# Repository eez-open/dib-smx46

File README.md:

The EEZ DIB SMX46 module features programmable 4 x 6 switch matrix,  dual analog outputs and one power relay. 

### Feature list

* On-board STM32F030C6T6 or STM32F031C4T6 MCU
* 2 x 16-pin dual row 3.81 mm connectors
* 2 x ADIB connectors (10-pin 2 mm)
* 4 x 6 switch matrix (24 two-wire crosspoints), max. 2 A 
* 1 x power relay, max. 8 A / 230 Vac
* 2 x analog output 0 - 10 V, 10 mV set resolution (12-bit)
* On-board +3.3 V LDO
* Firmware download via UART
* Optional SWD for debugging
* I2C EEPROM for storing board specific parameters
* Dimensions: 146 x 95 mm, 2-layer PCB

### Firmware repository

https://github.com/eez-open/dib-smx46-fw

### r1B5 prototype

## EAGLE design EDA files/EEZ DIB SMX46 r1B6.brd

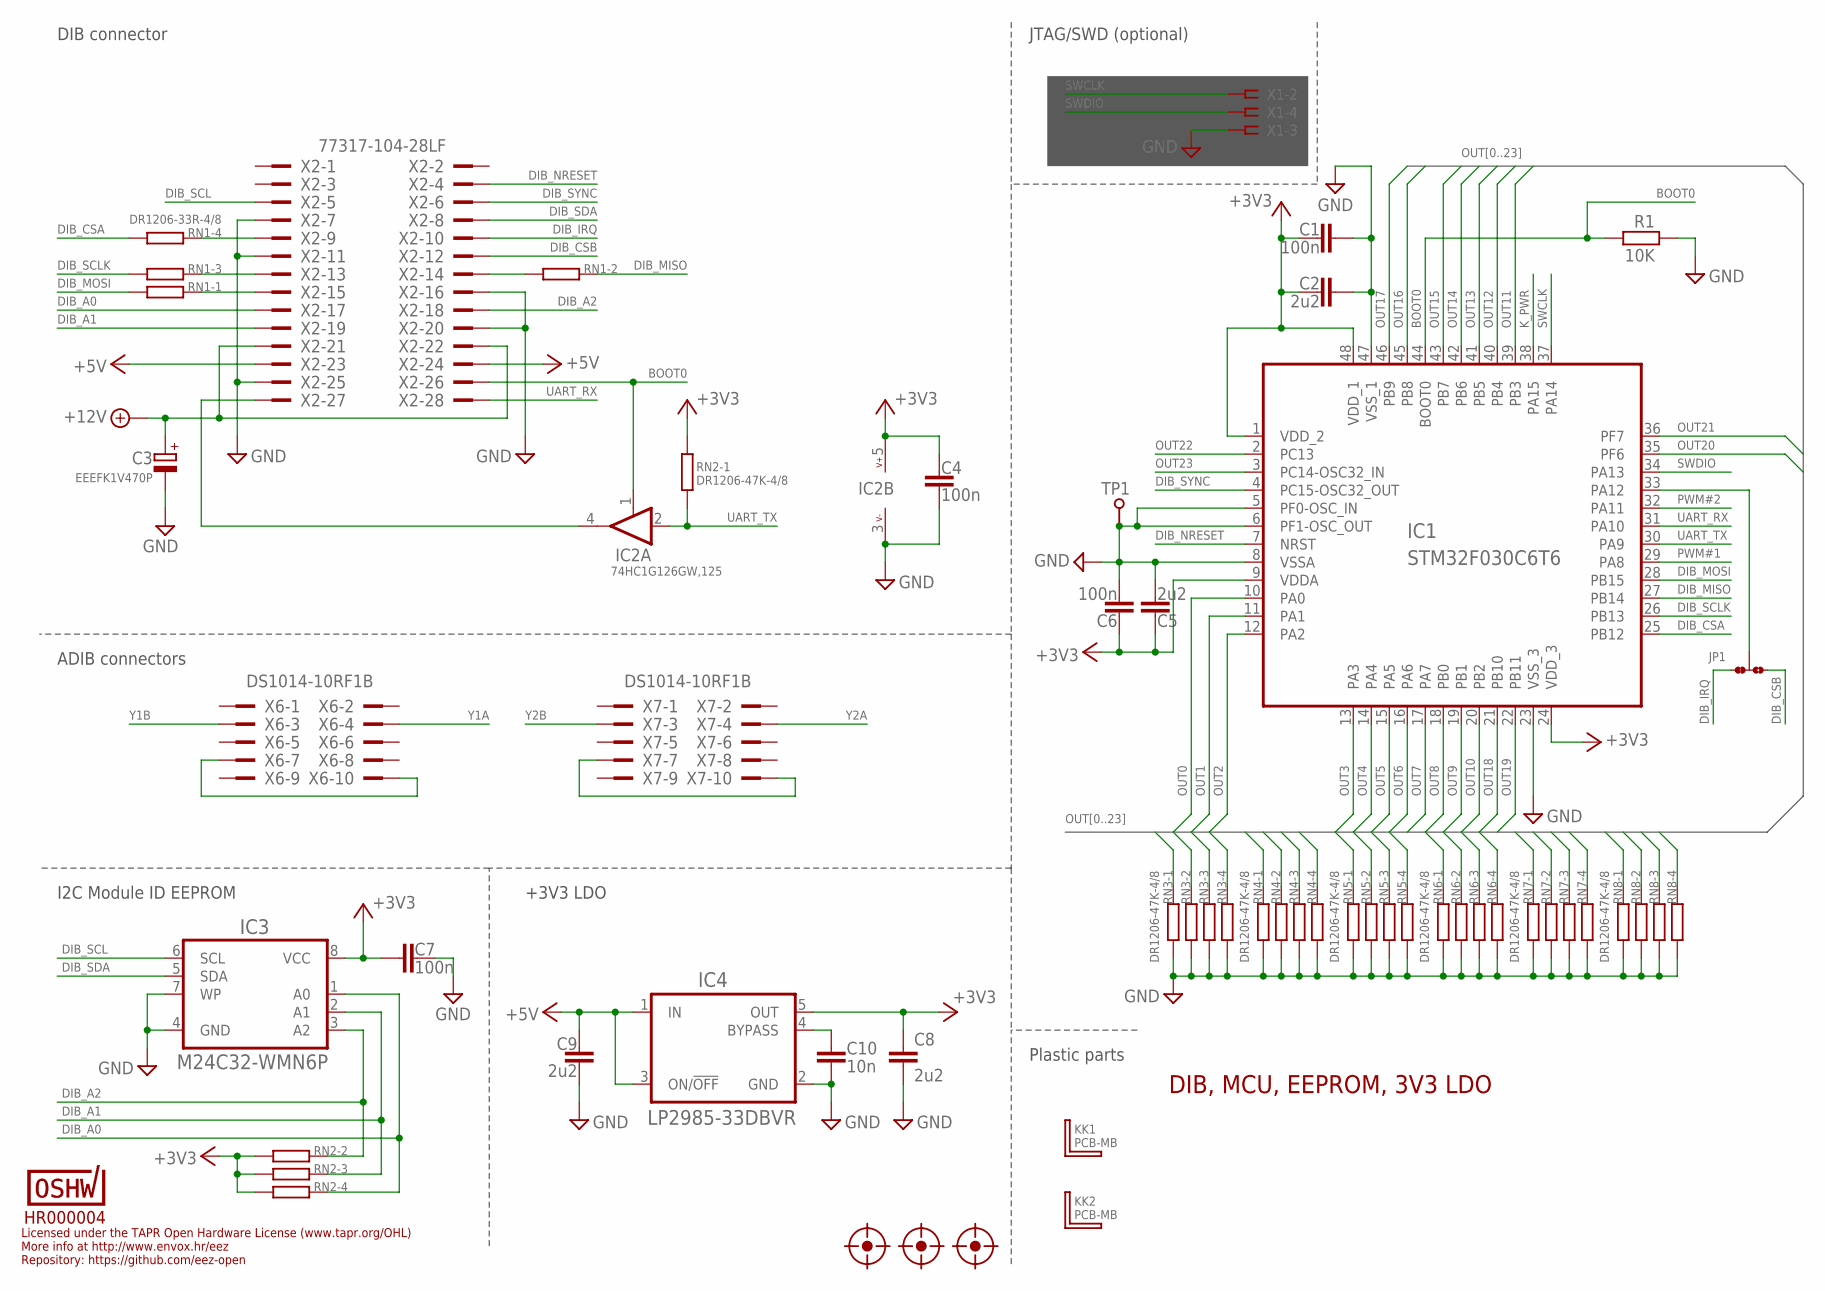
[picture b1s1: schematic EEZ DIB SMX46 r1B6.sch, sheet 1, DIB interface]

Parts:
C1, C4, C6, C7: 100n; C0603
C2, C5, C8, C9: 2u2; C0805
C3: EEEFK1V470P; CAPAE660X610N
C10: 10n; C0805
FM1, FM2, FM3: FIDUCIAL_2; FIDUCIAL_DUAL
IC1: STM32F030C6T6; LQFP-48
IC2: 74HC1G126GW,125; SOT65P210X110-5N
IC3: M24C32-WMN6P; SOIC127P600X173-8N
IC4: LP2985-33DBVR; SOT95P270X145-5N
JP1: JP3-CUT-0805-ROTATED; JP3-0805-CUT2
KK1, KK2: PCB-MB
R1: 10K; R0805
RN1: DR1206-33R-4/8; CAY16
RN2, RN3, RN4, RN5, RN6, RN7, RN8: DR1206-47K-4/8; CAY16
TP1: PCB_TEST_TABSHIELD; PCB_SHIELD_TAB
U$3: HR000004; CERT-SMALL-SILK
X1: N.C.; SSW-106-02-S-S
X2: 77317-104-28LF
X6, X7: DS1014-10RF1B

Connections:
+3V3: C1.2, C2.1, C4.1, C5.2, C6.1, C7.2, C8.1, IC1.1 (VDD_2), IC1.9 (VDDA), IC1.24 (VDD_3), IC1.48 (VDD_1), IC2.5 (V+), IC3.8 (VCC), IC4.5 (OUT), RN2.5 (2), RN2.6 (2), RN2.7 (2), RN2.8 (2); also elsewhere on the board
+5V: C9.2, IC4.1 (IN), IC4.3 (ON/!OFF), X2.23, X2.24; also elsewhere on the board
+12V: C3.1 (+), X2.21, X2.22; also elsewhere on the board
BOOT0: IC1.44 (BOOT0), IC2.1 (EN), R1.2, X2.26
DIB_A0: IC3.1 (A0), RN2.4 (1), X2.17
DIB_A1: IC3.2 (A1), RN2.3 (1), X2.19
DIB_A2: IC3.3 (A2), RN2.2 (1), X2.18
DIB_CSA: IC1.25 (PB12), RN1.4 (1)
DIB_CSB: JP1.NO, X2.12
DIB_IRQ: JP1.NC, X2.10
DIB_MISO: IC1.27 (PB14), RN1.2 (1)
DIB_MOSI: IC1.28 (PB15), RN1.1
DIB_NRESET: IC1.7 (NRST), X2.4
DIB_SCL: IC3.6 (SCL), X2.5
DIB_SCLK: IC1.26 (PB13), RN1.3 (1)
DIB_SDA: IC3.5 (SDA), X2.8
DIB_SYNC: IC1.4 (PC15-OSC32_OUT), X2.6
GND: C1.1, C2.2, C3.2 (-), C4.2, C5.1, C6.2, C7.1, C8.2, C9.1, C10.1, IC1.5 (PF0-OSC_IN), IC1.6 (PF1-OSC_OUT), IC1.8 (VSSA), IC1.23 (VSS_3), IC1.47 (VSS_1), IC2.3 (V-), IC3.4 (GND), IC3.7 (WP), IC4.2 (GND), R1.1, RN3.1, RN3.2 (1), RN3.3 (1), RN3.4 (1), RN4.1, RN4.2 (1), RN4.3 (1), RN4.4 (1), RN5.1, RN5.2 (1), RN5.3 (1), RN5.4 (1), RN6.1, RN6.2 (1), RN6.3 (1), RN6.4 (1), RN7.3 (1), RN7.4 (1), RN7.7 (2), RN7.8 (2), RN8.3 (1), RN8.4 (1), RN8.7 (2), RN8.8 (2), TP1.1, X1.3, X2.7, X2.11, X2.16, X2.20, X2.25; also elsewhere on the board
K_PWR: IC1.38 (PA15); also elsewhere on the board
unnamed: X6.7, X6.10
unnamed: X7.7, X7.10
unnamed: RN1.5 (2), X2.9
unnamed: C10.2, IC4.4 (BYPASS)
unnamed: IC2.4 (O), X2.27
unnamed: IC1.33 (PA12), JP1.COM
unnamed: RN1.6 (2), X2.13
unnamed: RN1.7 (2), X2.14
unnamed: RN1.8 (2), X2.15
OUT0: IC1.10 (PA0), RN3.8 (2); also elsewhere on the board
OUT1: IC1.11 (PA1), RN3.7 (2); also elsewhere on the board
OUT2: IC1.12 (PA2), RN6.8 (2); also elsewhere on the board
OUT3: IC1.13 (PA3), RN6.7 (2); also elsewhere on the board
OUT4: IC1.14 (PA4), RN3.5 (2); also elsewhere on the board
OUT5: IC1.15 (PA5), RN3.6 (2); also elsewhere on the board
OUT6: IC1.16 (PA6), RN6.5 (2); also elsewhere on the board
OUT7: IC1.17 (PA7), RN6.6 (2); also elsewhere on the board
OUT8: IC1.18 (PB0), RN4.7 (2); also elsewhere on the board
OUT9: IC1.19 (PB1), RN4.8 (2); also elsewhere on the board
OUT10: IC1.20 (PB2), RN7.6 (2); also elsewhere on the board
OUT11: IC1.39 (PB3), RN7.5 (2); also elsewhere on the board
OUT12: IC1.40 (PB4), RN4.5 (2); also elsewhere on the board
OUT13: IC1.41 (PB5), RN4.6 (2); also elsewhere on the board
OUT14: IC1.42 (PB6), RN7.2 (1); also elsewhere on the board
OUT15: IC1.43 (PB7), RN7.1; also elsewhere on the board
OUT16: IC1.45 (PB8), RN5.7 (2); also elsewhere on the board
OUT17: IC1.46 (PB9), RN5.8 (2); also elsewhere on the board
OUT18: IC1.21 (PB10), RN8.5 (2); also elsewhere on the board
OUT19: IC1.22 (PB11), RN8.6 (2); also elsewhere on the board
OUT20: IC1.35 (PF6), RN5.5 (2); also elsewhere on the board
OUT21: IC1.36 (PF7), RN5.6 (2); also elsewhere on the board
OUT22: IC1.2 (PC13), RN8.1; also elsewhere on the board
OUT23: IC1.3 (PC14-OSC32_IN), RN8.2 (1); also elsewhere on the board
PWM#1: IC1.29 (PA8); also elsewhere on the board
PWM#2: IC1.32 (PA11); also elsewhere on the board
SWCLK: IC1.37 (PA14), X1.2
SWDIO: IC1.34 (PA13), X1.4
UART_RX: IC1.31 (PA10), X2.28
UART_TX: IC1.30 (PA9), IC2.2 (I), RN2.1
Y1A: X6.4; also elsewhere on the board
Y1B: X6.3; also elsewhere on the board
Y2A: X7.4; also elsewhere on the board
Y2B: X7.3; also elsewhere on the board

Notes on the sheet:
Licensed under the TAPR Open Hardware License (www.tapr.org/OHL)
Repository: https://github.com/eez-open
More info at http://www.envox.hr/eez
DIB, MCU, EEPROM, 3V3 LDO
Plastic parts
I2C Module ID EEPROM
+3V3 LDO
JTAG/SWD (optional)
DIB connector
ADIB connectors

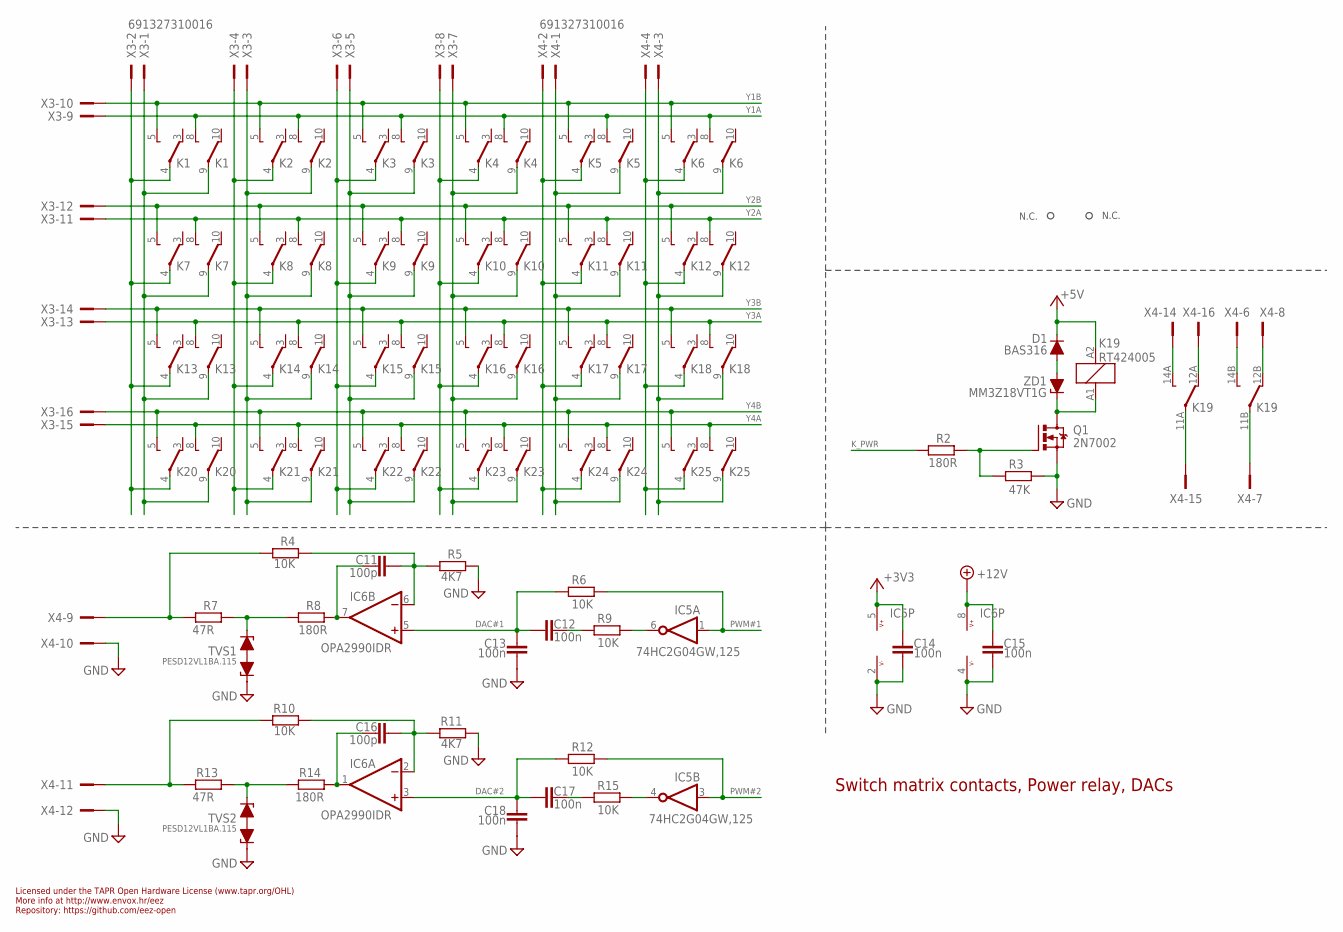
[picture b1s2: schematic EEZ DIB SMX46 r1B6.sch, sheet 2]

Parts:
C11, C16: 100p; C0805
C12, C13, C14, C15, C17, C18: 100n; C0603
D1: BAS316; SOD323-R
IC5: 74HC2G04GW,125; SOT65P210X110-6N
IC6: OPA2990IDR; SOIC127P600X173-8N
K1, K2, K3, K4, K5, K6, K7, K8, K9, K10, K11, K12, K13, K14, K15, K16, K17, K18, K20, K21, K22, K23, K24, K25: FTR-C1GA012G-B05; FTR-C1
K19: RT424005; RT-C/016A5_ROUND
Q1: 2N7002; SOT103P240X110-3N; MPN 2N7002-7-F
R2, R8, R14: 180R; R0805
R3: 47K; R0805
R4, R6, R9, R10, R12, R15: 10K; R0805
R5, R11: 4K7; R0805
R7, R13: 47R; R0805
TVS1, TVS2: PESD12VL1BA.115; SOD323-BIDIR
X3, X4: 691327310016
ZD1: MM3Z18VT1G; SOD323-R

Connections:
+3V3: C14.1, IC5.5 (V+); also elsewhere on the board
+5V: D1.C, K19.A2 (C1); also elsewhere on the board
+12V: C15.1, IC6.8 (V+); also elsewhere on the board
DAC#1: C12.1, C13.1, IC6.5 (+IN), R6.1
DAC#2: C17.1, C18.1, IC6.3 (+IN), R12.1
GND: C13.2, C14.2, C15.2, C18.2, IC5.2 (V-), IC6.4 (V-), Q1.2 (S), R3.1, R5.1, R11.1, TVS1.1, TVS2.1, X4.10, X4.12; also elsewhere on the board
ISET1: R7.1, R8.2, TVS1.2
ISET2: R13.1, R14.2, TVS2.2
K_PWR: R2.2; also elsewhere on the board
unnamed: K1.4, K7.4, K13.4, K20.4, X3.2
unnamed: K1.9, K7.9, K13.9, K20.9, X3.1
unnamed: K5.4, K11.4, K17.4, K24.4, X4.2
unnamed: K2.4, K8.4, K14.4, K21.4, X3.4
unnamed: K2.9, K8.9, K14.9, K21.9, X3.3
unnamed: K5.9, K11.9, K17.9, K24.9, X4.1
unnamed: K6.4, K12.4, K18.4, K25.4, X4.4
unnamed: K6.9, K12.9, K18.9, K25.9, X4.3
unnamed: K3.4, K9.4, K15.4, K22.4, X3.6
unnamed: K3.9, K9.9, K15.9, K22.9, X3.5
unnamed: K4.4, K10.4, K16.4, K23.4, X3.8
unnamed: K4.9, K10.9, K16.9, K23.9, X3.7
unnamed: R4.2, R7.2, X4.9
unnamed: C17.2, R15.1
unnamed: IC5.4 (O), R15.2
unnamed: C11.1, IC6.7 (OUT), R8.1
unnamed: C16.2, IC6.2 (-IN), R10.1, R11.2
unnamed: Q1.1 (G), R2.1, R3.2
unnamed: C16.1, IC6.1 (OUT), R14.1
unnamed: K19.11B, X4.7
unnamed: K19.12B (S), X4.8
unnamed: R10.2, R13.2, X4.11
unnamed: K19.14B (O), X4.6
unnamed: K19.11A, X4.15
unnamed: K19.12A (S), X4.16
unnamed: K19.14A (O), X4.14
unnamed: D1.A, ZD1.A
unnamed: K19.A1 (C2), Q1.3 (D), ZD1.C
unnamed: C12.2, R9.1
unnamed: C11.2, IC6.6 (-IN), R4.1, R5.2
unnamed: IC5.6 (O), R9.2
PWM#1: IC5.1 (I), R6.2; also elsewhere on the board
PWM#2: IC5.3 (I), R12.2; also elsewhere on the board
Y1A: K1.8 (O), K2.8 (O), K3.8 (O), K4.8 (O), K5.8 (O), K6.8 (O), X3.9; also elsewhere on the board
Y1B: K1.5 (O), K2.5 (O), K3.5 (O), K4.5 (O), K5.5 (O), K6.5 (O), X3.10; also elsewhere on the board
Y2A: K7.8 (O), K8.8 (O), K9.8 (O), K10.8 (O), K11.8 (O), K12.8 (O), X3.11; also elsewhere on the board
Y2B: K7.5 (O), K8.5 (O), K9.5 (O), K10.5 (O), K11.5 (O), K12.5 (O), X3.12; also elsewhere on the board
Y3A: K13.8 (O), K14.8 (O), K15.8 (O), K16.8 (O), K17.8 (O), K18.8 (O), X3.13
Y3B: K13.5 (O), K14.5 (O), K15.5 (O), K16.5 (O), K17.5 (O), K18.5 (O), X3.14
Y4A: K20.8 (O), K21.8 (O), K22.8 (O), K23.8 (O), K24.8 (O), K25.8 (O), X3.15
Y4B: K20.5 (O), K21.5 (O), K22.5 (O), K23.5 (O), K24.5 (O), K25.5 (O), X3.16

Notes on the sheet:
Licensed under the TAPR Open Hardware License (www.tapr.org/OHL)
Repository: https://github.com/eez-open
More info at http://www.envox.hr/eez
Switch matrix contacts, Power relay, DACs
N.C.

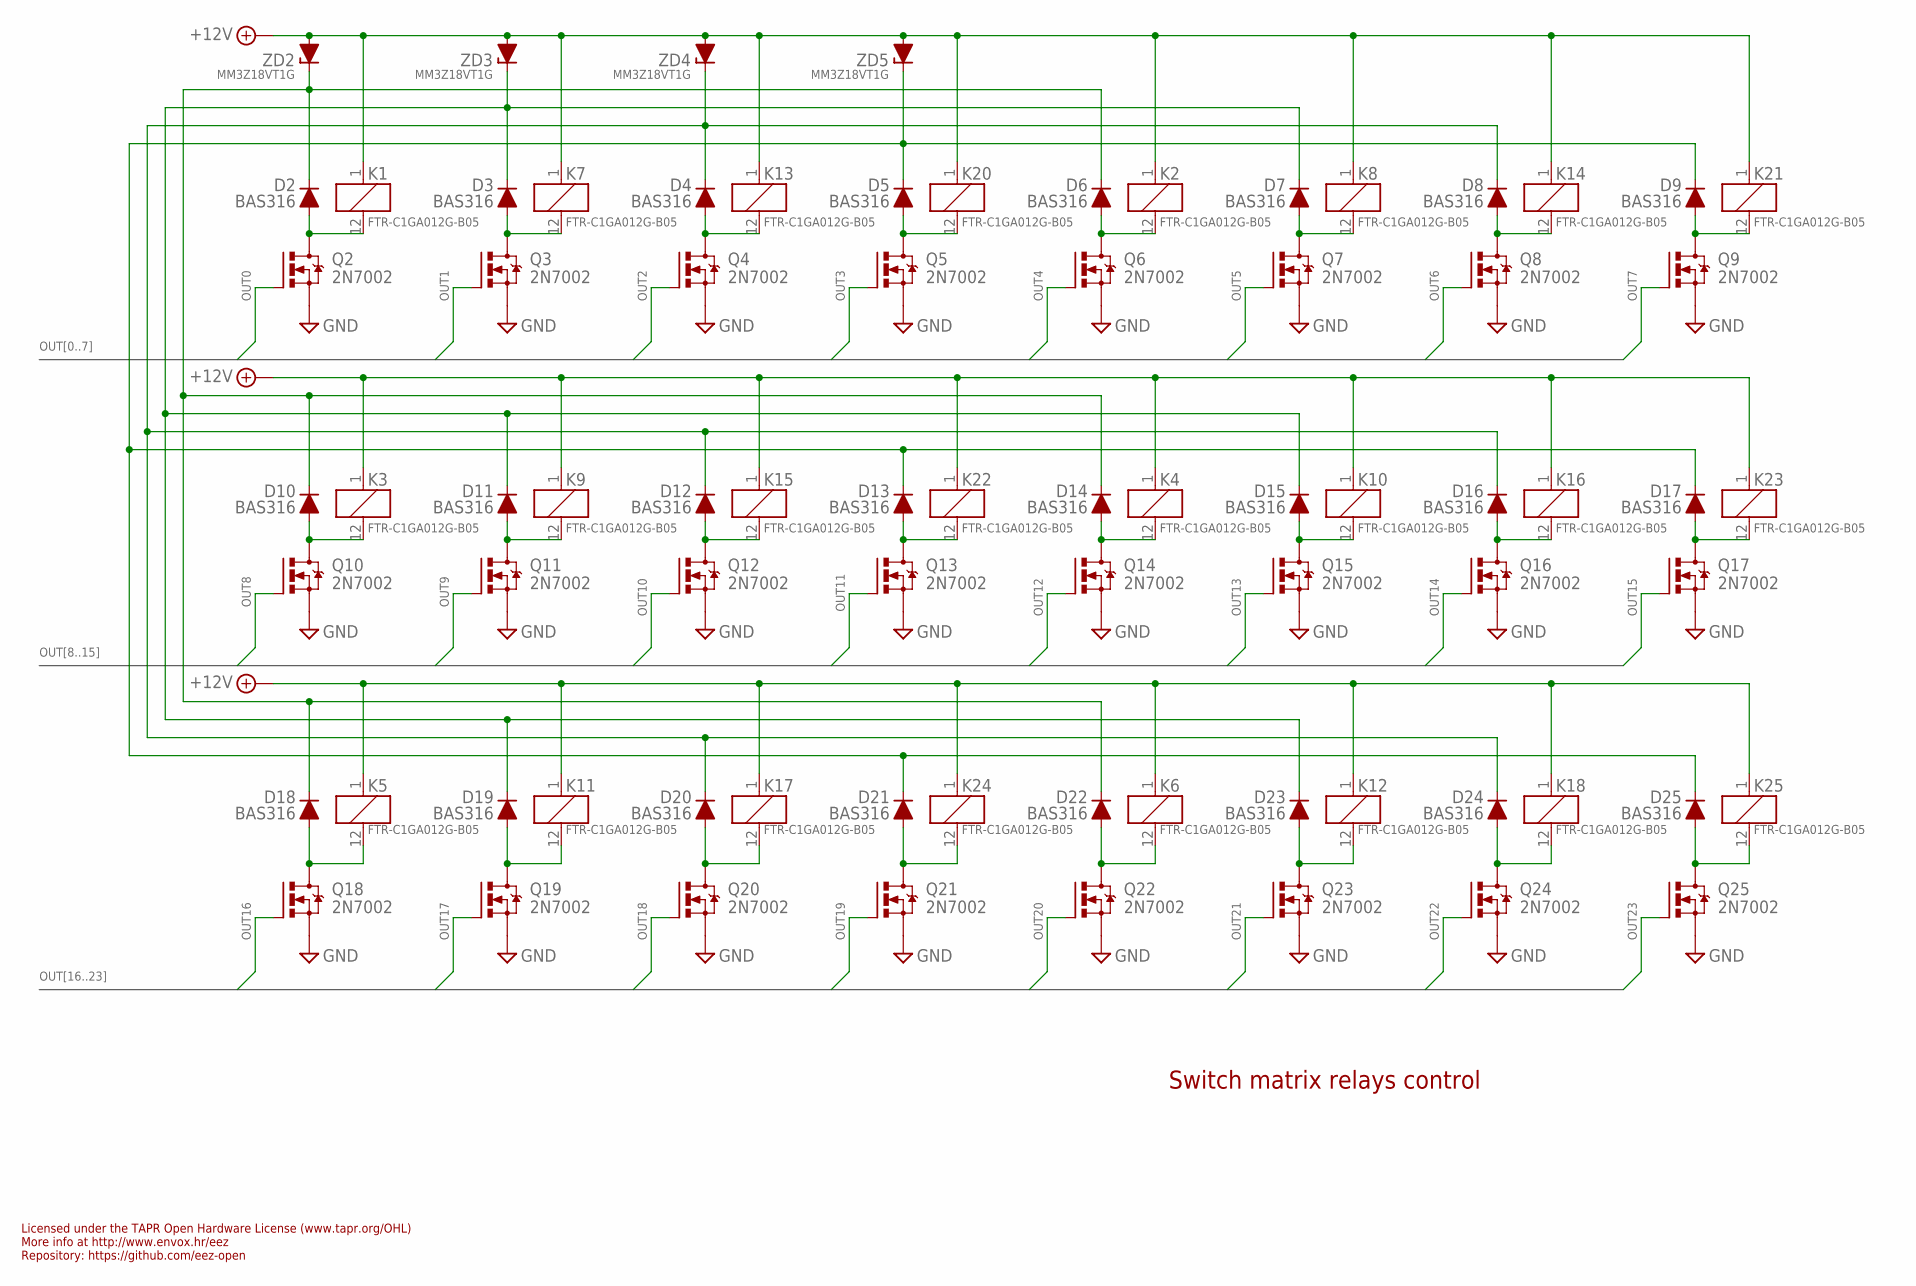
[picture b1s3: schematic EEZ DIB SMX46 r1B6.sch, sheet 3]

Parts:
D2, D3, D4, D5, D6, D7, D8, D9, D10, D11, D12, D13, D14, D15, D16, D17, D18, D19, D20, D21, D22, D23, D24, D25: BAS316; SOD323-R
K1, K2, K3, K4, K5, K6, K7, K8, K9, K10, K11, K12, K13, K14, K15, K16, K17, K18, K20, K21, K22, K23, K24, K25: FTR-C1GA012G-B05; FTR-C1
Q2, Q3, Q4, Q5, Q6, Q7, Q8, Q9, Q10, Q11, Q12, Q13, Q14, Q15, Q16, Q17, Q18, Q19, Q20, Q21, Q22, Q23, Q24, Q25: 2N7002; SOT103P240X110-3N; MPN 2N7002-7-F
ZD2, ZD3, ZD4, ZD5: MM3Z18VT1G; SOD323-R

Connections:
+12V: K1.1 (C1), K2.1 (C1), K3.1 (C1), K4.1 (C1), K5.1 (C1), K6.1 (C1), K7.1 (C1), K8.1 (C1), K9.1 (C1), K10.1 (C1), K11.1 (C1), K12.1 (C1), K13.1 (C1), K14.1 (C1), K15.1 (C1), K16.1 (C1), K17.1 (C1), K18.1 (C1), K20.1 (C1), K21.1 (C1), K22.1 (C1), K23.1 (C1), K24.1 (C1), K25.1 (C1), ZD2.A, ZD3.A, ZD4.A, ZD5.A; also elsewhere on the board
GND: Q2.2 (S), Q3.2 (S), Q4.2 (S), Q5.2 (S), Q6.2 (S), Q7.2 (S), Q8.2 (S), Q9.2 (S), Q10.2 (S), Q11.2 (S), Q12.2 (S), Q13.2 (S), Q14.2 (S), Q15.2 (S), Q16.2 (S), Q17.2 (S), Q18.2 (S), Q19.2 (S), Q20.2 (S), Q21.2 (S), Q22.2 (S), Q23.2 (S), Q24.2 (S), Q25.2 (S); also elsewhere on the board
unnamed: D2.C, D6.C, D10.C, D14.C, D18.C, D22.C, ZD2.C
unnamed: D3.C, D7.C, D11.C, D15.C, D19.C, D23.C, ZD3.C
unnamed: D4.C, D8.C, D12.C, D16.C, D20.C, D24.C, ZD4.C
unnamed: D5.C, D9.C, D13.C, D17.C, D21.C, D25.C, ZD5.C
unnamed: D4.A, K13.12 (C2), Q4.3 (D)
unnamed: D8.A, K14.12 (C2), Q8.3 (D)
unnamed: D10.A, K3.12 (C2), Q10.3 (D)
unnamed: D9.A, K21.12 (C2), Q9.3 (D)
unnamed: D11.A, K9.12 (C2), Q11.3 (D)
unnamed: D7.A, K8.12 (C2), Q7.3 (D)
unnamed: D12.A, K15.12 (C2), Q12.3 (D)
unnamed: D6.A, K2.12 (C2), Q6.3 (D)
unnamed: D13.A, K22.12 (C2), Q13.3 (D)
unnamed: D3.A, K7.12 (C2), Q3.3 (D)
unnamed: D14.A, K4.12 (C2), Q14.3 (D)
unnamed: D2.A, K1.12 (C2), Q2.3 (D)
unnamed: D15.A, K10.12 (C2), Q15.3 (D)
unnamed: D5.A, K20.12 (C2), Q5.3 (D)
unnamed: D16.A, K16.12 (C2), Q16.3 (D)
unnamed: D17.A, K23.12 (C2), Q17.3 (D)
unnamed: D19.A, K11.12 (C2), Q19.3 (D)
unnamed: D20.A, K17.12 (C2), Q20.3 (D)
unnamed: D21.A, K24.12 (C2), Q21.3 (D)
unnamed: D22.A, K6.12 (C2), Q22.3 (D)
unnamed: D23.A, K12.12 (C2), Q23.3 (D)
unnamed: D18.A, K5.12 (C2), Q18.3 (D)
unnamed: D24.A, K18.12 (C2), Q24.3 (D)
unnamed: D25.A, K25.12 (C2), Q25.3 (D)
OUT0: Q2.1 (G); also elsewhere on the board
OUT1: Q3.1 (G); also elsewhere on the board
OUT2: Q4.1 (G); also elsewhere on the board
OUT3: Q5.1 (G); also elsewhere on the board
OUT4: Q6.1 (G); also elsewhere on the board
OUT5: Q7.1 (G); also elsewhere on the board
OUT6: Q8.1 (G); also elsewhere on the board
OUT7: Q9.1 (G); also elsewhere on the board
OUT8: Q10.1 (G); also elsewhere on the board
OUT9: Q11.1 (G); also elsewhere on the board
OUT10: Q12.1 (G); also elsewhere on the board
OUT11: Q13.1 (G); also elsewhere on the board
OUT12: Q14.1 (G); also elsewhere on the board
OUT13: Q15.1 (G); also elsewhere on the board
OUT14: Q16.1 (G); also elsewhere on the board
OUT15: Q17.1 (G); also elsewhere on the board
OUT16: Q18.1 (G); also elsewhere on the board
OUT17: Q19.1 (G); also elsewhere on the board
OUT18: Q20.1 (G); also elsewhere on the board
OUT19: Q21.1 (G); also elsewhere on the board
OUT20: Q22.1 (G); also elsewhere on the board
OUT21: Q23.1 (G); also elsewhere on the board
OUT22: Q24.1 (G); also elsewhere on the board
OUT23: Q25.1 (G); also elsewhere on the board

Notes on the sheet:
Licensed under the TAPR Open Hardware License (www.tapr.org/OHL)
Repository: https://github.com/eez-open
More info at http://www.envox.hr/eez
Switch matrix relays control

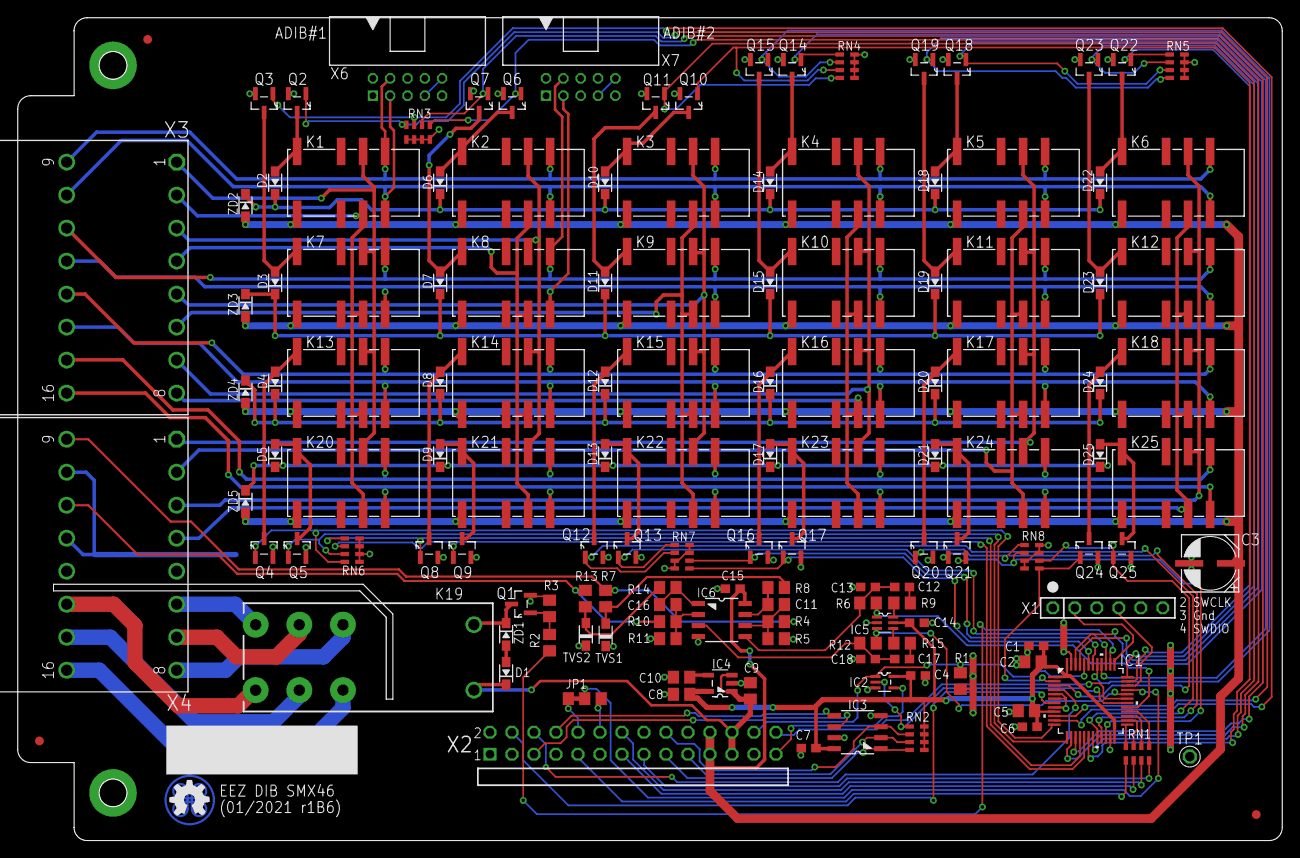
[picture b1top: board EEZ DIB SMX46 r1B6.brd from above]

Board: 2 copper layers, 146.0 x 95.0 mm, 144 parts (1 on the bottom side), 129 nets.

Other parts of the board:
EEZ_SIGNATURE: SIGNATURESMALL; SIGNATURE_5MM

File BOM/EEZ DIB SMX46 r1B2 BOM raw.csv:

Partlist exported from /home/denis/BACKUP/EEZ/PCB/Programmable PSU/DIB/EEZ DIB SMX46 r1B2.sch at 6.4.2020. 12:41

Assembly variant: ''

Qty Value            Device             Parts                                                                                                                                      
1   1u               C-EUC0805          C6                                                                                                                                         
25  2N7002           2N7002             Q1, Q2, Q3, Q4, Q5, Q6, Q7, Q8, Q9, Q10, Q11, Q12, Q13, Q14, Q15, Q16, Q17, Q18, Q19, Q20, Q21, Q22, Q23, Q24, Q25                         
1   2u2              C-EUC0805          C8                                                                                                                                         
2   4K7              R-EU_R0805         R4, R10                                                                                                                                    
2   4u7              C-EUC0805          C2, C9                                                                                                                                     
7   10K              R-EU_R0805         R1, R3, R5, R8, R9, R11, R14                                                                                                               
1   10n              C-EUC0805          C10                                                                                                                                        
1   47K              R-EU_R0805         R2                                                                                                                                         
2   47R              R-EU_R0805         R6, R12                                                                                                                                    
1   74HC1G126GW,125  74HC1G126GW,125    IC2                                                                                                                                        
1   74HC2G04GW,125   74HC2G04           IC5                                                                                                                                        
10  100n             C-EUC0603          C1, C4, C5, C7, C12, C13, C14, C15, C17, C18                                                                                               
2   100p             C-EUC0805          C11, C16                                                                                                                                   
2   180R             R-EU_R0805         R7, R13                                                                                                                                    
1   77317-104-28LF   77317-104-28LF     X2                                                                                                                                         
2   691327310016     691327310016       X3, X4                                                                                                                                     
25  BAS316           DIODESOD323R       D1, D2, D3, D4, D5, D6, D7, D8, D9, D10, D11, D12, D13, D14, D15, D16, D17, D18, D19, D20, D21, D22, D23, D24, D25                         
1   DR1206-10K-4/8   R_ARRAY4           RN2                                                                                                                                        
1   DR1206-33R-4/8   R_ARRAY4           RN1                                                                                                                                        
6   DR1206-47K-4/8   R_ARRAY4           RN3, RN4, RN5, RN6, RN7, RN8                                                                                                               
1   EEEFK1V470P      ECAPPANASONIC_H    C3                                                                                                                                         
2   FIDUCIAL_2       FIDUCIAL_2         FM1, FM2                                                                                                                                   
24  FTR-C1GA012G-B05 FTR-C1             K1, K2, K3, K4, K5, K6, K7, K8, K9, K10, K11, K12, K13, K14, K15, K16, K17, K18, K19, K20, K21, K22, K23, K24                              
1   LP2985-33DBVR    LP2985             IC4                                                                                                                                        
1   M24C32-WMN6P     AT24CXXSOIC8       IC3                                                                                                                                        
25  MM3Z18VT1G       ZENER-DIODESOD323R ZD1, ZD2, ZD3, ZD4, ZD5, ZD6, ZD7, ZD8, ZD9, ZD10, ZD11, ZD12, ZD13, ZD14, ZD15, ZD16, ZD17, ZD18, ZD19, ZD20, ZD21, ZD22, ZD23, ZD24, ZD25
1   OPA2170          TL072SOIC8         IC6                                                                                                                                        
2   PCB-MB           PCB-MB             KK1, KK2                                                                                                                                   
2   PESD12VL1BA.115  PESDXL1BA          TVS1, TVS2                                                                                                                                 
1   RT424005         RELAY_RT314012-2   K_PWR                                                                                                                                      
1   SSW-106-02-S-S   SSW-106-02-S-S     X1                                                                                                                                         
1   STM32F030C6T6    STM32F030C6T6      IC1

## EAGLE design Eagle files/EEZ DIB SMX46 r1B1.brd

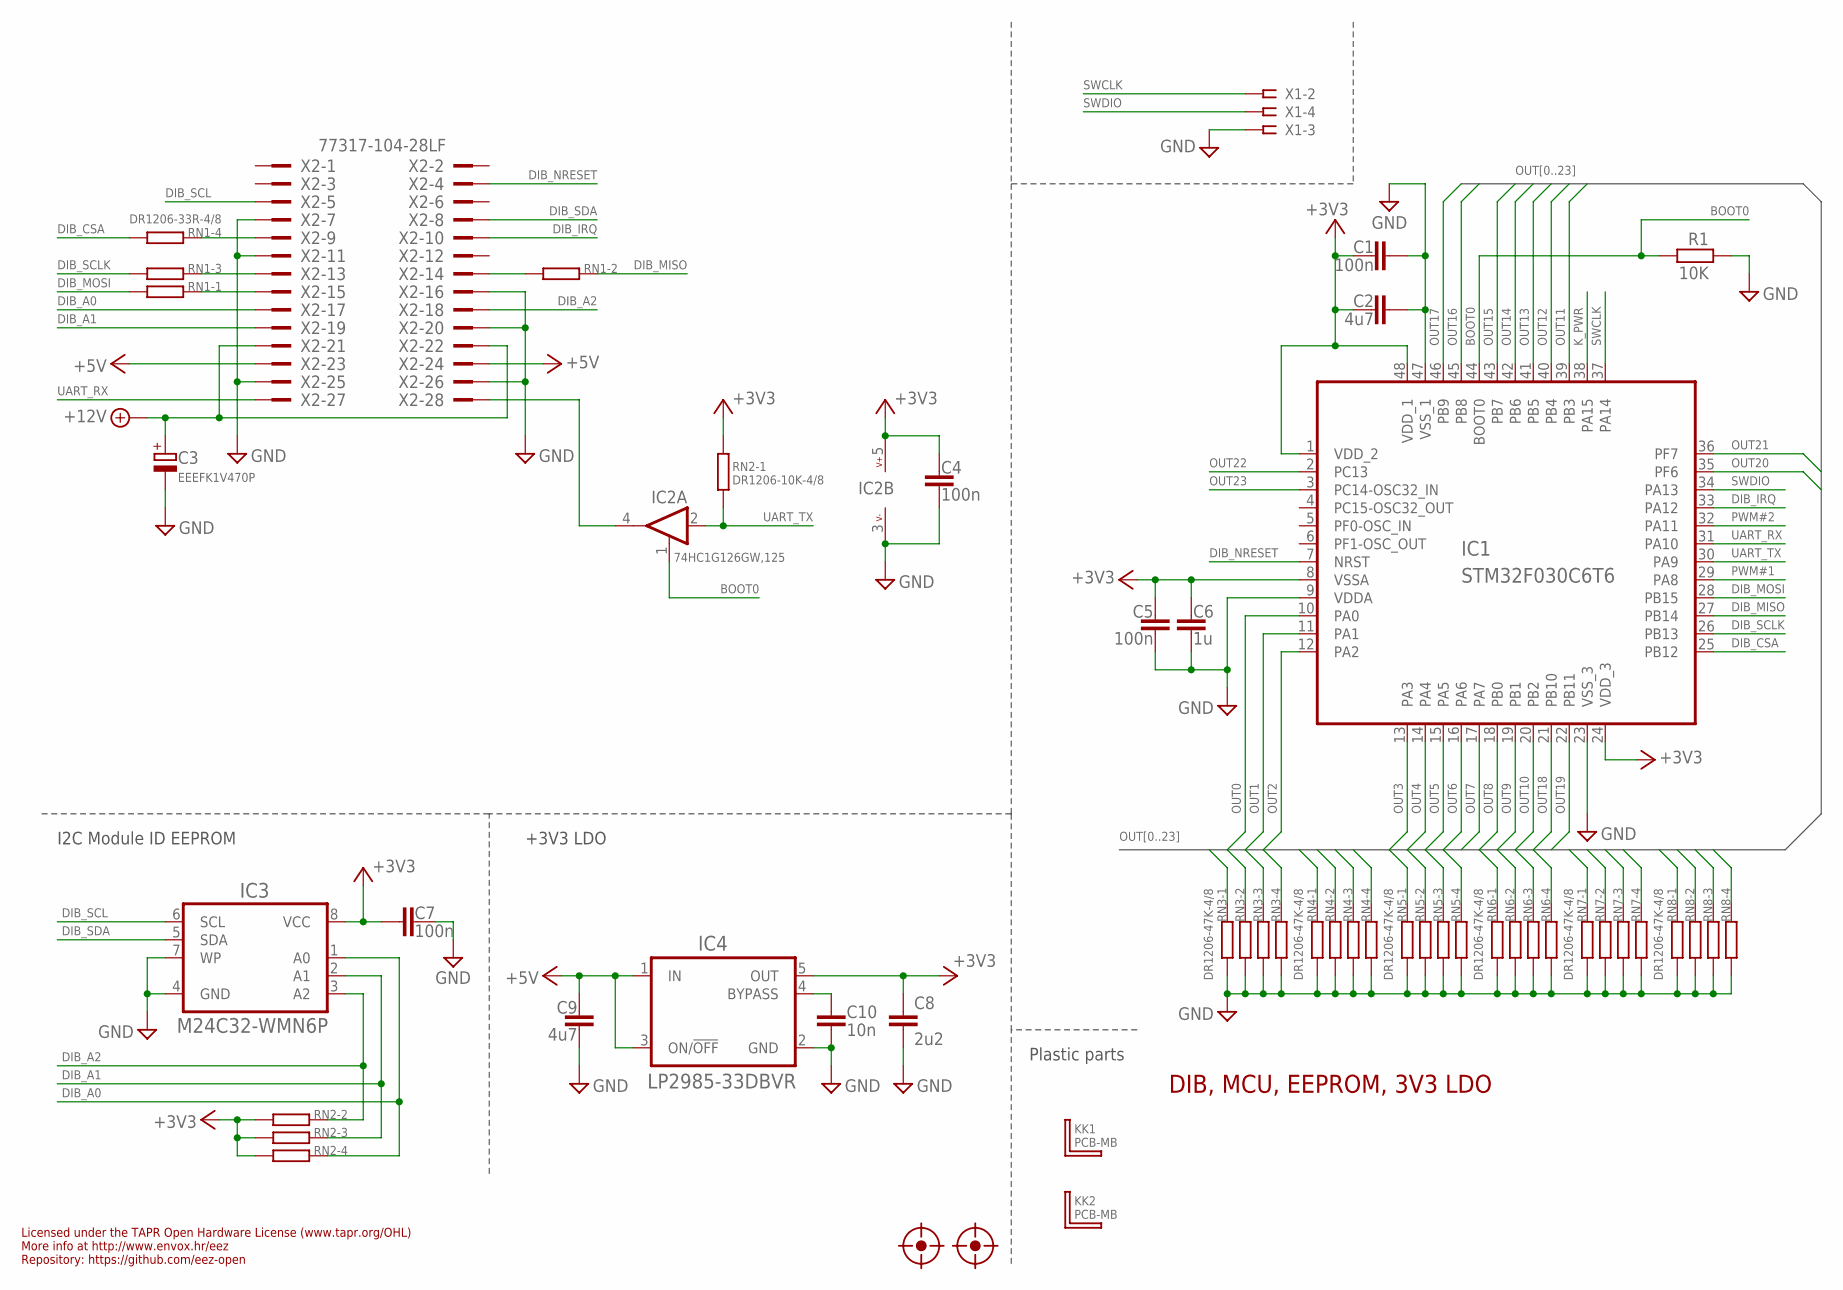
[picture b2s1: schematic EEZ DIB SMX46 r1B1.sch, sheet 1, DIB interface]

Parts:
C1, C4, C5, C7: 100n; C0603
C2, C9: 4u7; C1206
C3: EEEFK1V470P; CAPAE660X610N
C6: 1u; C0805
C8: 2u2; C0805
C10: 10n; C0805
FM1, FM2: FIDUCIAL_2; FIDUCIAL_DUAL
IC1: STM32F030C6T6; LQFP-48
IC2: 74HC1G126GW,125; SOT65P210X110-5N
IC3: M24C32-WMN6P; SOIC127P600X173-8N
IC4: LP2985-33DBVR; SOT95P270X145-5N
KK1, KK2: PCB-MB
R1: 10K; R0805
RN1: DR1206-33R-4/8; CAY16
RN2: DR1206-10K-4/8; CAY16
RN3, RN4, RN5, RN6, RN7, RN8: DR1206-47K-4/8; CAY16
X1: SSW-106-02-S-S
X2: 77317-104-28LF

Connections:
+3V3: C1.2, C2.1, C4.1, C5.1, C6.2, C7.2, C8.1, IC1.1 (VDD_2), IC1.8 (VSSA), IC1.24 (VDD_3), IC1.48 (VDD_1), IC2.5 (V+), IC3.8 (VCC), IC4.5 (OUT), RN2.5 (2), RN2.6 (2), RN2.7 (2), RN2.8 (2); also elsewhere on the board
+5V: C9.2, IC4.1 (IN), IC4.3 (ON/!OFF), X2.23, X2.24; also elsewhere on the board
+12V: C3.1 (+), X2.21, X2.22; also elsewhere on the board
BOOT0: IC1.44 (BOOT0), IC2.1 (EN), R1.2
DIB_A0: IC3.1 (A0), RN2.4 (1), X2.17
DIB_A1: IC3.2 (A1), RN2.3 (1), X2.19
DIB_A2: IC3.3 (A2), RN2.2 (1), X2.18
DIB_CSA: IC1.25 (PB12), RN1.4 (1)
DIB_IRQ: IC1.33 (PA12), X2.10
DIB_MISO: IC1.27 (PB14), RN1.2 (1)
DIB_MOSI: IC1.28 (PB15), RN1.1
DIB_NRESET: IC1.7 (NRST), X2.4
DIB_SCL: IC3.6 (SCL), X2.5
DIB_SCLK: IC1.26 (PB13), RN1.3 (1)
DIB_SDA: IC3.5 (SDA), X2.8
GND: C1.1, C2.2, C3.2 (-), C4.2, C5.2, C6.1, C7.1, C8.2, C9.1, C10.1, IC1.9 (VDDA), IC1.23 (VSS_3), IC1.47 (VSS_1), IC2.3 (V-), IC3.4 (GND), IC3.7 (WP), IC4.2 (GND), R1.1, RN3.1, RN3.2 (1), RN3.3 (1), RN3.4 (1), RN4.1, RN4.2 (1), RN4.3 (1), RN4.4 (1), RN5.1, RN5.2 (1), RN5.3 (1), RN5.4 (1), RN6.1, RN6.2 (1), RN6.3 (1), RN6.4 (1), RN7.3 (1), RN7.4 (1), RN7.7 (2), RN7.8 (2), RN8.3 (1), RN8.4 (1), RN8.7 (2), RN8.8 (2), X1.3, X2.7, X2.11, X2.16, X2.20, X2.25, X2.26; also elsewhere on the board
K_PWR: IC1.38 (PA15); also elsewhere on the board
unnamed: RN1.5 (2), X2.9
unnamed: C10.2, IC4.4 (BYPASS)
unnamed: IC2.4 (O), X2.28
unnamed: RN1.6 (2), X2.13
unnamed: RN1.7 (2), X2.14
unnamed: RN1.8 (2), X2.15
OUT0: IC1.10 (PA0), RN3.8 (2); also elsewhere on the board
OUT1: IC1.11 (PA1), RN3.7 (2); also elsewhere on the board
OUT2: IC1.12 (PA2), RN6.8 (2); also elsewhere on the board
OUT3: IC1.13 (PA3), RN6.7 (2); also elsewhere on the board
OUT4: IC1.14 (PA4), RN3.5 (2); also elsewhere on the board
OUT5: IC1.15 (PA5), RN3.6 (2); also elsewhere on the board
OUT6: IC1.16 (PA6), RN6.5 (2); also elsewhere on the board
OUT7: IC1.17 (PA7), RN6.6 (2); also elsewhere on the board
OUT8: IC1.18 (PB0), RN4.7 (2); also elsewhere on the board
OUT9: IC1.19 (PB1), RN4.8 (2); also elsewhere on the board
OUT10: IC1.20 (PB2), RN7.6 (2); also elsewhere on the board
OUT11: IC1.39 (PB3), RN7.5 (2); also elsewhere on the board
OUT12: IC1.40 (PB4), RN4.5 (2); also elsewhere on the board
OUT13: IC1.41 (PB5), RN4.6 (2); also elsewhere on the board
OUT14: IC1.42 (PB6), RN7.2 (1); also elsewhere on the board
OUT15: IC1.43 (PB7), RN7.1; also elsewhere on the board
OUT16: IC1.45 (PB8), RN5.7 (2); also elsewhere on the board
OUT17: IC1.46 (PB9), RN5.8 (2); also elsewhere on the board
OUT18: IC1.21 (PB10), RN8.5 (2); also elsewhere on the board
OUT19: IC1.22 (PB11), RN8.6 (2); also elsewhere on the board
OUT20: IC1.35 (PF6), RN5.5 (2); also elsewhere on the board
OUT21: IC1.36 (PF7), RN5.6 (2); also elsewhere on the board
OUT22: IC1.2 (PC13), RN8.1; also elsewhere on the board
OUT23: IC1.3 (PC14-OSC32_IN), RN8.2 (1); also elsewhere on the board
PWM#1: IC1.29 (PA8); also elsewhere on the board
PWM#2: IC1.32 (PA11); also elsewhere on the board
SWCLK: IC1.37 (PA14), X1.2
SWDIO: IC1.34 (PA13), X1.4
UART_RX: IC1.31 (PA10), X2.27
UART_TX: IC1.30 (PA9), IC2.2 (I), RN2.1

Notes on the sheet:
Licensed under the TAPR Open Hardware License (www.tapr.org/OHL)
Repository: https://github.com/eez-open
More info at http://www.envox.hr/eez
DIB, MCU, EEPROM, 3V3 LDO
Plastic parts
I2C Module ID EEPROM
+3V3 LDO

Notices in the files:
parts and their libraries:
EEZ_DIB: This work is licensed under the TAPR Open Hardware License.
